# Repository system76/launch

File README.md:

# System76 Launch Configurable Keyboard

The System76 Launch Configurable Keyboard is designed to provide the ultimate
user controlled keyboard experience, with open source mechanical and electrical
design, open source firmware and associated software, and a large number of
user configuration opportunities. It is registered open source hardware with
[OSHWA UID US001062](https://certification.oshwa.org/us001062.html).

- [Mechanical Design](#mechanical-design)
- [Electrical Design](#electrical-design)
- [Firmware and Software](#firmware-and-software)

## Mechanical Design

### Open Source Chassis

The Launch chassis is licensed CC-BY-SA-4.0 and can be viewed in the
[chassis](./chassis/) folder using [FreeCAD](https://www.freecad.org).

### Milled Aluminum

The chassis is milled from two solid blocks of aluminum and powder coated to
provide excellent fit and finish. Each pocket, port, and hole is designed and
precisely machined so that swapping switches and plugging in cables is easy and
secure for the user.

### Detachable Lift Bar

The included lift bar can be magnetically secured to add 15 degrees of angle to
your keyboard for ergonomics.

### Innovative Layout

The layout is designed to provide a large number of remapping opportunities.
The default layout can be viewed
[here](http://www.keyboard-layout-editor.com/#/gists/8ec5e9026d616ebad6b2c7e9d943e7c0),
and the extra keys included can be viewed
[here](http://www.keyboard-layout-editor.com/#/gists/a3ad8710b27f78fd938077b2bf6d3ef5).

### Swappable Keycaps

The keycaps are PBT material with a dye sublimation legend and XDA profile to
provide excellent feel and lifespan. Extras are provided for common replacements
and color preference. An included keycap puller can be used to move and replace
the keycaps.

### Swappable Switches

The switches are mounted in sockets that support any RGB switch with an MX
compatible footprint. Examples are the Cherry MX RGB switches and the Kailh
BOX switches. Switches can be removed easily at any time with the included
switch puller.

## Electrical Design

### Open Source PCB

The Launch PCB is licensed GPLv3 and can be viewed in the
[pcb](./pcb/) folder using [KiCad](https://kicad.org/).

### Integrated Dock

Launch connects to a computer using the included USB-C to USB-C cable or USB-C
to USB-A cable. It supports USB 3.2 Gen 2 with speeds up to 10 Gbps with either
cable, provided the computer supports these speeds. It provides 2 USB-C and 2
USB-A connectors that also support USB 3.2 Gen 2, with the 10 Gbps bandwidth
shared between them on demand.

### Independent RGB Lighting

Each switch has an RGB LED that is independently controlled by firmware. This
allows for a number of RGB LED patterns to be selected.

### N-Key Rollover

The keyboard matrix uses diodes on all intersections, providing full independent
scanning of each key position.

## Firmware and Software

### Open Source Firmware

The Launch firmware is based on [QMK](https://github.com/system76/qmk_firmware),
licensed GPLv2, and the latest version is linked in the `firmware` submodule.

### Open Source Software

Projects that integrate with Launch are open source software, such as the
[System76 Keyboard Configurator](https://github.com/pop-os/keyboard-configurator),
licensed GPLv3, and [fwupd](https://github.com/fwupd/fwupd/), licensed LGPLv2.1.

### Easy Remapping

The keyboard can be remapped at runtime using the
[System76 Keyboard Configurator](https://github.com/pop-os/keyboard-configurator).
This utility runs on Linux, Mac OS, and Windows.

### Firmware Updates

Firmware updates are supported through the
[fwupd](https://github.com/fwupd/fwupd/) project, and are distributed using the
related Linux Vendor Firmware Service. Settings are stored on EEPROM and are
maintained through firmware updates.

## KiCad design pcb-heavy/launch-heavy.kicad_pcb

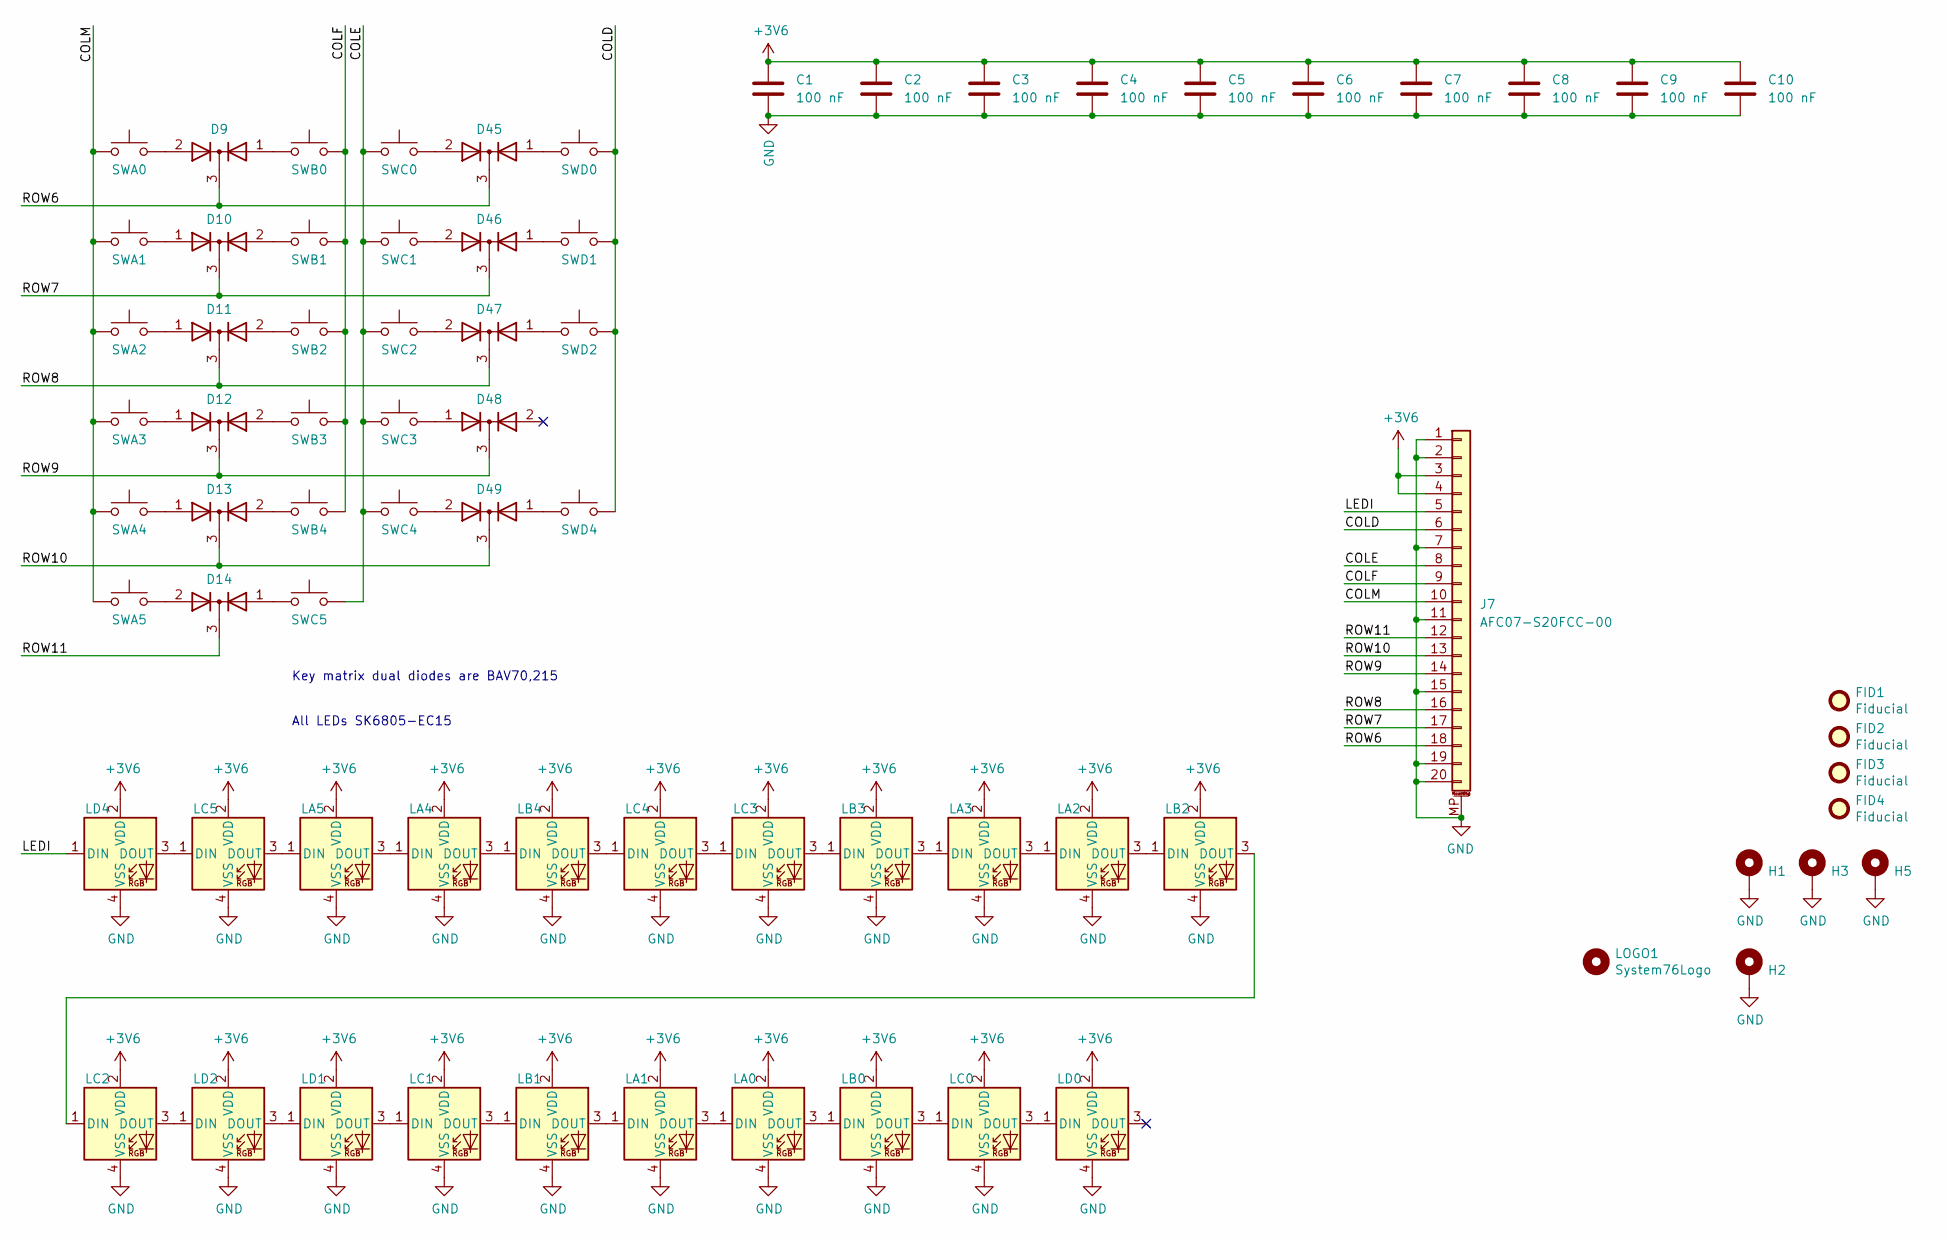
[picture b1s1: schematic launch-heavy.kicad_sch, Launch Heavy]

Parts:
C1, C2, C3, C4, C5, C6, C7, C8, C9, C10: 100 nF; C_0603_1608Metric
D9, D10, D11, D12, D13, D14, D45, D46, D47, D48, D49: BAV70,215; SOT-23
FID1, FID2, FID3, FID4: Fiducial; Fiducial_0.75mm_Mask1.5mm
H1, H2, H3, H5: MountingHole_Pad; MountingHole
J7: AFC07-S20FCC-00
LA0, LA1, LA2, LA3, LA4, LA5: SK6805-EC15; LED_SK6805-EC15
LB0, LB1, LB2, LB3, LB4: SK6805-EC15; LED_SK6805-EC15
LC0, LC1, LC2, LC3, LC4, LC5: SK6805-EC15; LED_SK6805-EC15
LD0, LD1, LD2, LD4: SK6805-EC15; LED_SK6805-EC15
LOGO1: System76Logo; System76
SWA0, SWA1, SWA2, SWA3, SWA4, SWA5: CPG151101S11; Kailh_socket_MX
SWB0, SWB1, SWB2, SWB3, SWB4: CPG151101S11; Kailh_socket_MX
SWC0, SWC1, SWC2, SWC3, SWC4, SWC5: CPG151101S11; Kailh_socket_MX
SWD0, SWD1, SWD2, SWD4: CPG151101S11; Kailh_socket_MX

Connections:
+3V6: C1.2, C2.2, C3.2, C4.2, C5.2, C6.2, C7.2, C8.2, C9.2, C10.2, J7.3, J7.4, LA0.2 (VDD), LA1.2 (VDD), LA2.2 (VDD), LA3.2 (VDD), LA4.2 (VDD), LA5.2 (VDD), LB0.2 (VDD), LB1.2 (VDD), LB2.2 (VDD), LB3.2 (VDD), LB4.2 (VDD), LC0.2 (VDD), LC1.2 (VDD), LC2.2 (VDD), LC3.2 (VDD), LC4.2 (VDD), LC5.2 (VDD), LD0.2 (VDD), LD1.2 (VDD), LD2.2 (VDD), LD4.2 (VDD)
/COLD: J7.6, SWD0.1, SWD1.1, SWD2.1, SWD4.1
/COLE: J7.8, SWC0.1, SWC1.1, SWC2.1, SWC3.1, SWC4.1, SWC5.1
/COLF: J7.9, SWB0.1, SWB1.1, SWB2.1, SWB3.1, SWB4.1
/COLM: J7.10, SWA0.1, SWA1.1, SWA2.1, SWA3.1, SWA4.1, SWA5.1
/LEDI: J7.5, LD4.1 (DIN)
/ROW6: D9.3 (K), D45.3 (K), J7.18
/ROW7: D10.3 (K), D46.3 (K), J7.17
/ROW8: D11.3 (K), D47.3 (K), J7.16
/ROW9: D12.3 (K), D48.3 (K), J7.14
/ROW10: D13.3 (K), D49.3 (K), J7.13
/ROW11: D14.3 (K), J7.12
GND: C1.1, C2.1, C3.1, C4.1, C5.1, C6.1, C7.1, C8.1, C9.1, C10.1, H1.1, H2.1, H3.1, H5.1, J7.1, J7.2, J7.7, J7.11, J7.15, J7.19, J7.20, J7.MP (MountPin), LA0.4 (VSS), LA1.4 (VSS), LA2.4 (VSS), LA3.4 (VSS), LA4.4 (VSS), LA5.4 (VSS), LB0.4 (VSS), LB1.4 (VSS), LB2.4 (VSS), LB3.4 (VSS), LB4.4 (VSS), LC0.4 (VSS), LC1.4 (VSS), LC2.4 (VSS), LC3.4 (VSS), LC4.4 (VSS), LC5.4 (VSS), LD0.4 (VSS), LD1.4 (VSS), LD2.4 (VSS), LD4.4 (VSS)
unnamed: D9.1 (A), SWB0.2
unnamed: D9.2 (A), SWA0.2
unnamed: D10.1 (A), SWA1.2
unnamed: D10.2 (A), SWB1.2
unnamed: D11.1 (A), SWA2.2
unnamed: D11.2 (A), SWB2.2
unnamed: D12.1 (A), SWA3.2
unnamed: D12.2 (A), SWB3.2
unnamed: D13.1 (A), SWA4.2
unnamed: D13.2 (A), SWB4.2
unnamed: D14.1 (A), SWC5.2
unnamed: D14.2 (A), SWA5.2
unnamed: D45.1 (A), SWD0.2
unnamed: D45.2 (A), SWC0.2
unnamed: D46.1 (A), SWD1.2
unnamed: D46.2 (A), SWC1.2
unnamed: D47.1 (A), SWD2.2
unnamed: D47.2 (A), SWC2.2
unnamed: D48.1 (A), SWC3.2
unnamed: D49.1 (A), SWD4.2
unnamed: D49.2 (A), SWC4.2
unnamed: LA0.1 (DIN), LA1.3 (DOUT)
unnamed: LA0.3 (DOUT), LB0.1 (DIN)
unnamed: LA1.1 (DIN), LB1.3 (DOUT)
unnamed: LA2.1 (DIN), LA3.3 (DOUT)
unnamed: LA2.3 (DOUT), LB2.1 (DIN)
unnamed: LA3.1 (DIN), LB3.3 (DOUT)
unnamed: LA4.1 (DIN), LA5.3 (DOUT)
unnamed: LA4.3 (DOUT), LB4.1 (DIN)
unnamed: LA5.1 (DIN), LC5.3 (DOUT)
unnamed: LB0.3 (DOUT), LC0.1 (DIN)
unnamed: LB1.1 (DIN), LC1.3 (DOUT)
unnamed: LB2.3 (DOUT), LC2.1 (DIN)
unnamed: LB3.1 (DIN), LC3.3 (DOUT)
unnamed: LB4.3 (DOUT), LC4.1 (DIN)
unnamed: LC0.3 (DOUT), LD0.1 (DIN)
unnamed: LC1.1 (DIN), LD1.3 (DOUT)
unnamed: LC2.3 (DOUT), LD2.1 (DIN)
unnamed: LC3.1 (DIN), LC4.3 (DOUT)
unnamed: LC5.1 (DIN), LD4.3 (DOUT)
unnamed: LD1.1 (DIN), LD2.3 (DOUT)

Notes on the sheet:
Key matrix dual diodes are BAV70,215
All LEDs SK6805-EC15

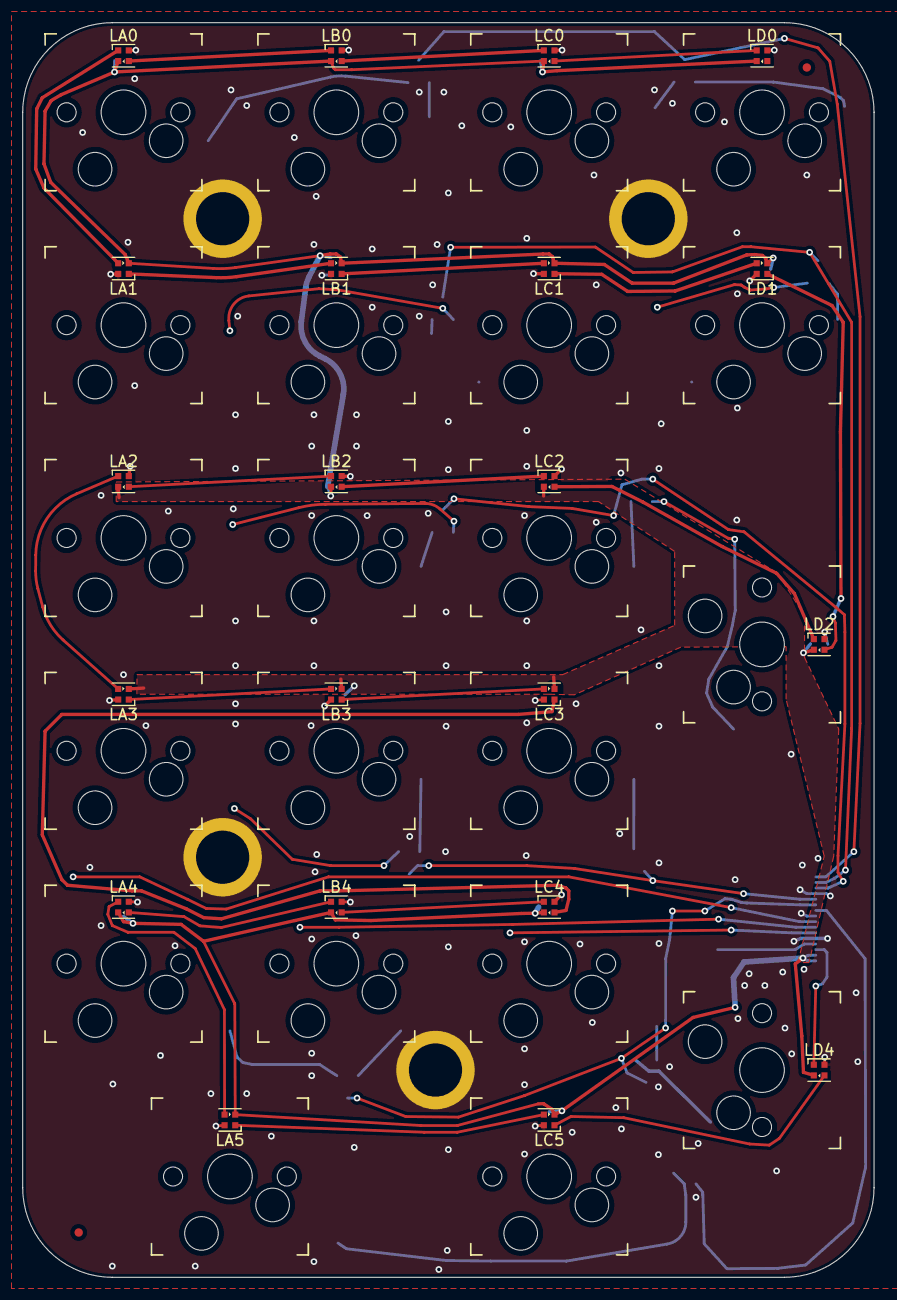
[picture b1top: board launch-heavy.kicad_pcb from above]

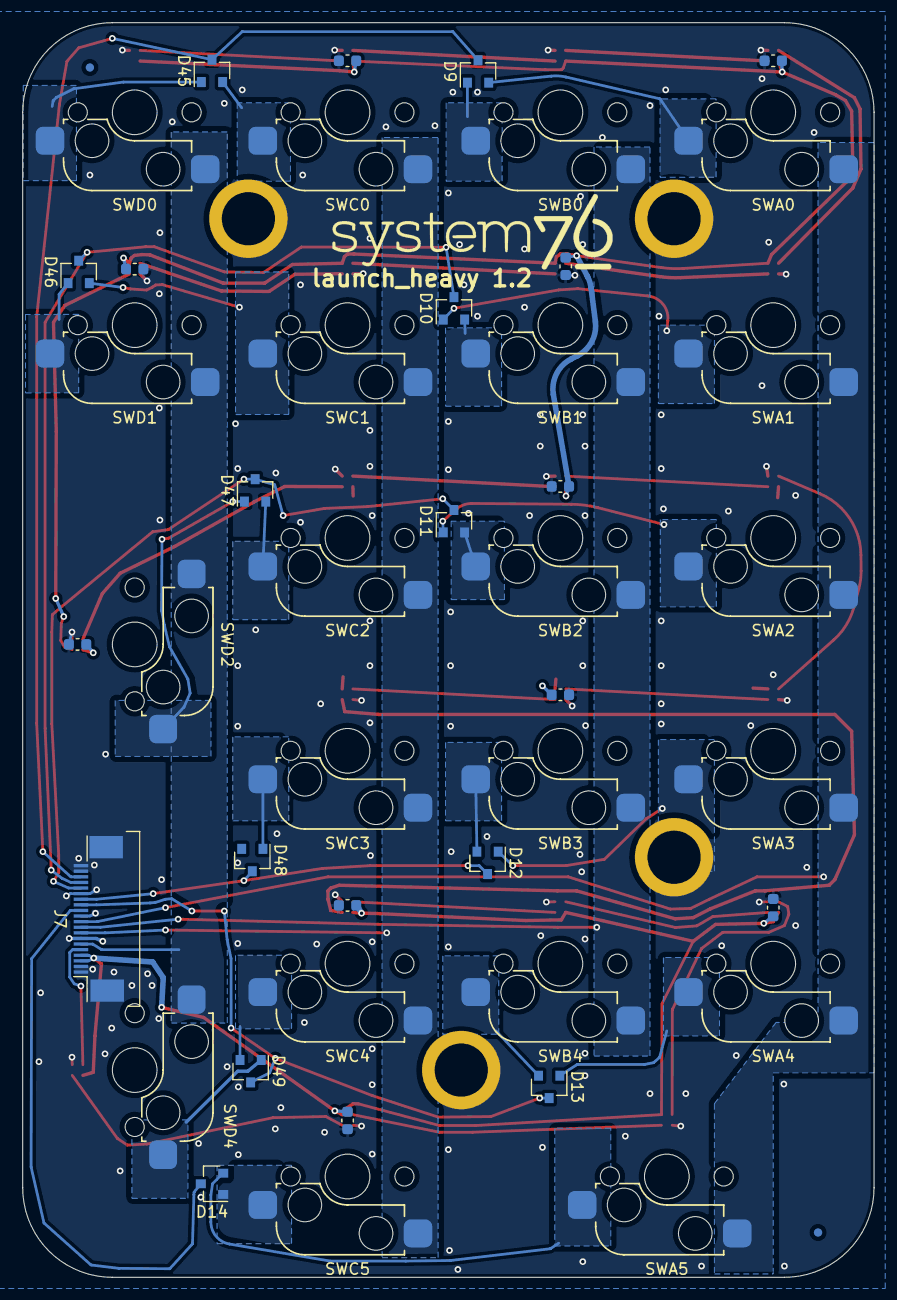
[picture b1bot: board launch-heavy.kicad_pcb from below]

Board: 2 copper layers, 76.0 x 112.0 mm, 73 parts (46 on the bottom side), 54 nets.

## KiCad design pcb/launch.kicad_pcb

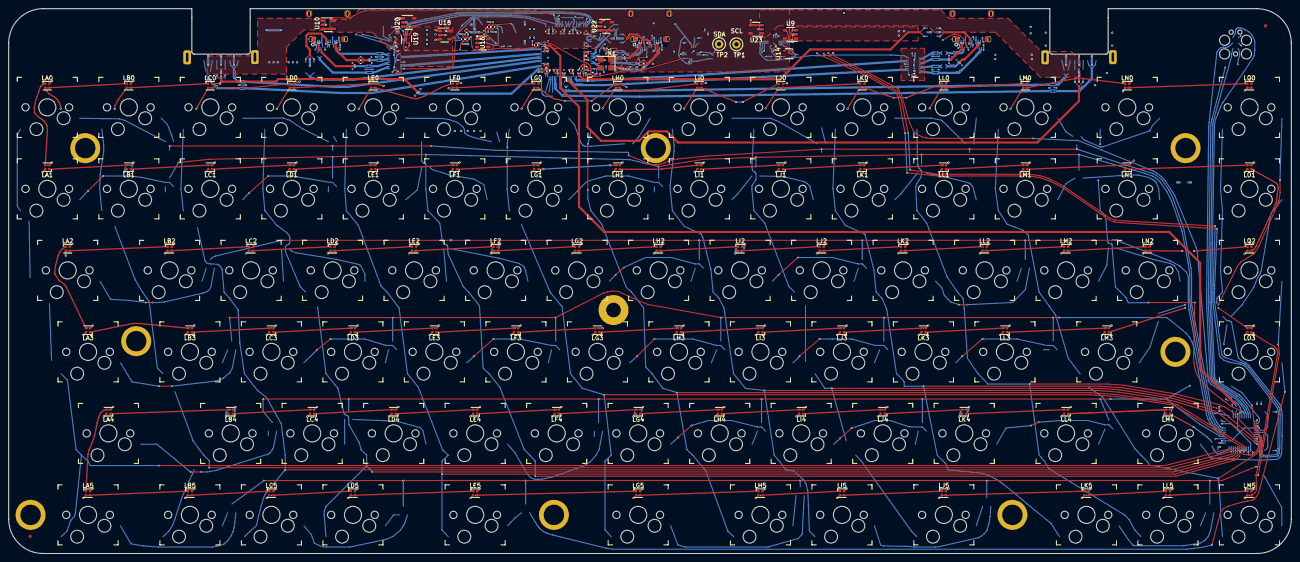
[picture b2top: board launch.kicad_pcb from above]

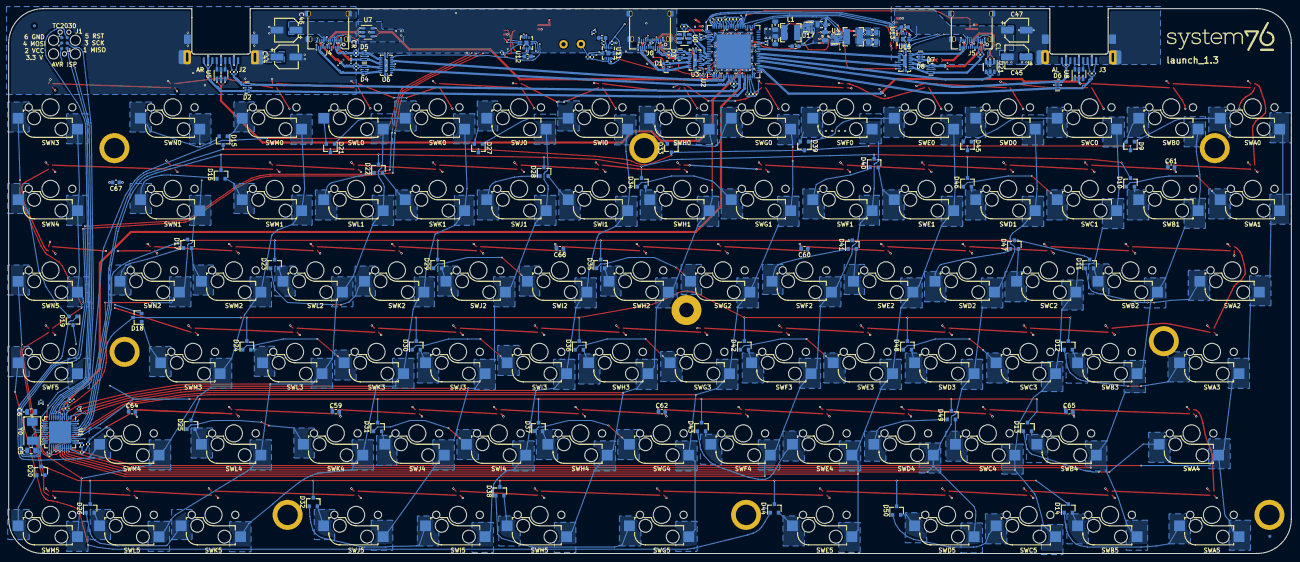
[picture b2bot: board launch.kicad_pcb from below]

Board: 4 copper layers, 299.0 x 127.0 mm, 372 parts (229 on the bottom side), 337 nets.

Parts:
C0, C1, C2, C3, C4, C8, C9, C10, C11, C12, C13, C14, C15, C16, C17, C18, C19, C20, C21, C22, C23, C24, C28, C29, C30, C31, C36, C37, C38, C39, C40, C41, C42, C43, C51, C52, C53, C54, C55, C56, C57, C58, C63: 0.1uF; C_0402_1005Metric
C5, C6: 22pF; C_0805_2012Metric
C7: 1 nF; C_0402_1005Metric
C25, C26, C27, C33, C59, C60, C61, C62, C64, C65, C66, C67: 2.2 uF; C_0603_1608Metric
C32, C34, C35, C48, C49, C50: 22 uF; C_0805_2012Metric
C44, C45, C46, C47: APXF6R3ARA151ME40G; CP_Elec_5x3.9
C68, C69: 330 pF; C_0402_1005Metric
D1, D2, D3, D4, D5, D6, D7, D8: PUSB3FR4Z; DFN-10_1x2.5mm_P0.5mm
D9, D10, D11, D12, D13, D14, D15, D16, D17, D18, D19, D20, D21, D22, D23, D24, D25, D26, D27, D28, D29, D30, D31, D32, D33, D34, D35, D36, D37, D38, D39, D40, D41, D42, D43, D44, D45, D46, D47, D48, D49, D50: BAV70,215; SOT-23
FID1, FID2, FID3, FID4: Fiducial; Fiducial_0.75mm_Mask1.5mm
H1, H2, H3, H4, H5, H6, H7, H8, H9: MountingHole_Pad; MountingHole
J0, J4, J5: 12401598E4#2A; USB_C_Receptacle_Amphenol_12401610E4-2A
J1: DNP; Tag-Connect_TC2030-IDC-FP_2x03_P1.27mm_Vertical
J2, J3: 1003-002-01100; USB3_A_CnC_Tech_1003-002-01100
L1, L2: SRN4018TA-2R2M; L_Bourns-SRN4018
LA0, LA1, LA2, LA3, LA4, LA5: SK6805-EC15; LED_SK6805-EC15
LB0, LB1, LB2, LB3, LB4, LB5: SK6805-EC15; LED_SK6805-EC15
LC0, LC1, LC2, LC3, LC4, LC5: SK6805-EC15; LED_SK6805-EC15
LD0, LD1, LD2, LD3, LD4, LD5: SK6805-EC15; LED_SK6805-EC15
LE0, LE1, LE2, LE3, LE4, LE5: SK6805-EC15; LED_SK6805-EC15
LF0, LF1, LF2, LF3, LF4: SK6805-EC15; LED_SK6805-EC15
LG0, LG1, LG2, LG3, LG4, LG5: SK6805-EC15; LED_SK6805-EC15
LH0, LH1, LH2, LH3, LH4, LH5: SK6805-EC15; LED_SK6805-EC15
LI0, LI1, LI2, LI3, LI4, LI5: SK6805-EC15; LED_SK6805-EC15
LJ0, LJ1, LJ2, LJ3, LJ4, LJ5: SK6805-EC15; LED_SK6805-EC15
LK0, LK1, LK2, LK3, LK4, LK5: SK6805-EC15; LED_SK6805-EC15
LL0, LL1, LL2, LL3, LL4, LL5: SK6805-EC15; LED_SK6805-EC15
LM0, LM1, LM2, LM3, LM4, LM5: SK6805-EC15; LED_SK6805-EC15
LN0, LN1, LN2: SK6805-EC15; LED_SK6805-EC15
LO0, LO1, LO2, LO3: SK6805-EC15; LED_SK6805-EC15
LOGO1: System76Logo; System76
R1: 12 k; R_0402_1005Metric
R2, R3: 22; R_0402_1005Metric
R4, R5, R6, R7, R8, R11, R15, R23, R26, R31, R32: 10 k; R_0402_1005Metric
R9, R10, R14: 9.1 k; R_0402_1005Metric
R12, R13, R19, R20: 200 k; R_0402_1005Metric
R16, R17, R29, R30: 100 k; R_0402_1005Metric
R18, R21: 43 k; R_0402_1005Metric
R22, R25, R28: 52.3 k; R_0402_1005Metric
R24, R33, R34: DNP; R_0402_1005Metric
R27: 499; R_0402_1005Metric
SWA0, SWA1, SWA2, SWA3, SWA4, SWA5: CPG151101S11; Kailh_socket_MX
SWB0, SWB1, SWB2, SWB3, SWB4, SWB5: CPG151101S11; Kailh_socket_MX
SWC0, SWC1, SWC2, SWC3, SWC4, SWC5: CPG151101S11; Kailh_socket_MX
SWD0, SWD1, SWD2, SWD3, SWD4, SWD5: CPG151101S11; Kailh_socket_MX
SWE0, SWE1, SWE2, SWE3, SWE4, SWE5: CPG151101S11; Kailh_socket_MX
SWF0, SWF1, SWF2, SWF3, SWF4, SWF5: CPG151101S11; Kailh_socket_MX
SWG0, SWG1, SWG2, SWG3, SWG4, SWG5: CPG151101S11; Kailh_socket_MX
SWH0, SWH1, SWH2, SWH3, SWH4, SWH5: CPG151101S11; Kailh_socket_MX
SWI0, SWI1, SWI2, SWI3, SWI4, SWI5: CPG151101S11; Kailh_socket_MX
SWJ0, SWJ1, SWJ2, SWJ3, SWJ4, SWJ5: CPG151101S11; Kailh_socket_MX
SWK0, SWK1, SWK2, SWK3, SWK4, SWK5: CPG151101S11; Kailh_socket_MX
SWL0, SWL1, SWL2, SWL3, SWL4, SWL5: CPG151101S11; Kailh_socket_MX
SWM0, SWM1, SWM2, SWM3, SWM4, SWM5: CPG151101S11; Kailh_socket_MX
SWN0, SWN1, SWN2, SWN3, SWN4, SWN5: CPG151101S11; Kailh_socket_MX
TP1, TP2: DNP; TestPoint_Loop_D1.80mm_Drill1.0mm_Beaded
U0, U5, U7, U8, U21: USBLC6-2SC6; SOT-23-6
U1: ATmega32U4-MU; QFN-44-1EP_7x7mm_P0.5mm_EP5.2x5.2mm
U2: USB7216C; QFN-100-1EP_12x12mm_P0.4mm_EP8x8mm
U3, U6, U15: CBTL02043ABQ,115; QFN-20-1EP_2.5x4.5mm_P0.5mm_EP1x3mm
U4, U17: AP3441LSHE-7B; W-DFN2020-8_Type_C
U9, U10, U20, U22, U23: AP22811AW5-7; SOT-23-5
U11: PTN5110DHQ; QFN-16-1EP_2.6x2.6mm_P0.4mm_EP1.1x1mm
U12, U13: PTN5110THQ; QFN-16-1EP_2.6x2.6mm_P0.4mm_EP1.1x1mm
U14, U19: SN74LVC1G08DCKR; SOT-353_SC-70-5
U16: AP22811AW5-7‎; SOT-23-5
U18: LP5907MFX-3.3; SOT-23-5
X1: ECS-3225MV-250-BN-TR; Oscillator_SMD_SeikoEpson_SG8002CE-4Pin_3.2x2.5mm
Y0: ECS-160-18-23G-JGN-TR; Crystal_SMD_0603-2Pin_6.0x3.5mm

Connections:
+1V1: C8.1, C17.1, C18.1, C19.1, C20.1, C21.1, C22.1, C23.1, C24.1, C34.1, C50.1, C68.1, L1.2, R14.1, U2.9, U2.18, U2.25, U2.31, U2.38, U2.55, U2.78, U2.85, U2.93
+3V3: C0.2, C1.1, C2.1, C3.1, C33.1, C36.1, C37.1, C38.1, C39.1, C40.1, C41.1, C42.1, C43.1, C55.1, C56.1, C57.1, C58.1, C63.1, J1.2, R5.1, R6.1, R7.1, R9.1, R10.1, R23.1, R31.1, R32.1, U1.6, U1.14, U1.24, U1.34, U1.44, U2.26, U2.43, U2.53, U2.62, U2.67, U2.79, U2.81, U2.82, U2.88, U2.99, U3.1, U3.6, U3.10, U6.1, U6.6, U6.10, U11.3, U11.11, U12.3, U12.11, U13.3, U13.11, U15.1, U15.6, U15.10, U18.5, X1.1, X1.4
+3V6: C35.1, C49.1, C59.1, C60.1, C61.1, C62.1, C64.1, C65.1, C66.1, C67.1, C69.1, L2.2, LA0.2, LA1.2, LA2.2, LA3.2, LA4.2, LA5.2, LB0.2, LB1.2, LB2.2, LB3.2, LB4.2, LB5.2, LC0.2, LC1.2, LC2.2, LC3.2, LC4.2, LC5.2, LD0.2, LD1.2, LD2.2, LD3.2, LD4.2, LD5.2, LE0.2, LE1.2, LE2.2, LE3.2, LE4.2, LE5.2, LF0.2, LF1.2, LF2.2, LF3.2, LF4.2, LG0.2, LG1.2, LG2.2, LG3.2, LG4.2, LG5.2, LH0.2, LH1.2, LH2.2, LH3.2, LH4.2, LH5.2, LI0.2, LI1.2, LI2.2, LI3.2, LI4.2, LI5.2, LJ0.2, LJ1.2, LJ2.2, LJ3.2, LJ4.2, LJ5.2, LK0.2, LK1.2, LK2.2, LK3.2, LK4.2, LK5.2, LL0.2, LL1.2, LL2.2, LL3.2, LL4.2, LL5.2, LM0.2, LM1.2, LM2.2, LM3.2, LM4.2, LM5.2, LN0.2, LN1.2, LN2.2, LO0.2, LO1.2, LO2.2, LO3.2, R25.1, U18.1, U18.3
/AVR_SCL: R9.2, TP1.1, U1.18, U2.75, U11.8, U12.8, U13.8
/AVR_SDA: R10.2, TP2.1, U1.19, U2.76, U11.7, U12.7, U13.7
/USB/AL_D+: U2.28, U8.1
/USB/AL_D-: U2.27, U8.3
/USB/AL_ESD_D+: J3.3, U8.6
/USB/AL_ESD_D-: J3.2, U8.4
/USB/AL_RX+: D6.2, D6.9, J3.6, U2.32
/USB/AL_RX-: D6.1, D6.10, J3.5, U2.33
/USB/AL_TX+: C54.1, D6.5, D6.6, U2.29
/USB/AL_TX-: C53.1, D6.4, D6.7, U2.30
/USB/AL_VBUS: C45.1, J3.1, U8.5, U10.1
/USB/AR_D+: U2.15, U5.1
/USB/AR_D-: U2.14, U5.3
/USB/AR_ESD_D+: J2.3, U5.6
/USB/AR_ESD_D-: J2.2, U5.4
/USB/AR_RX+: D2.2, D2.9, J2.6, U2.19
/USB/AR_RX-: D2.1, D2.10, J2.5, U2.20
/USB/AR_TX+: C52.1, D2.5, D2.6, U2.16
/USB/AR_TX-: C51.1, D2.4, D2.7, U2.17
/USB/AR_VBUS: C44.1, J2.1, U5.5, U23.1
/USB/AVR_USB_D+: R2.2, U2.42
/USB/AVR_USB_D-: R3.1, U2.41
/USB/AVR_VBUS: C4.1, R24.2, U1.7, U22.1
/USB/CL_BYP: C27.2, U13.4, U19.5
/USB/CL_CC1: J5.A5, U13.13
/USB/CL_CC2: J5.B5, U13.14
/USB/CL_D0+: J5.A6, J5.B6, U21.1
/USB/CL_D0-: J5.A7, J5.B7, U21.3
/USB/CL_D+: U2.34, U21.6
/USB/CL_D-: U2.35, U21.4
/USB/CL_EN: U19.4, U20.4
/USB/CL_RX1+: D7.2, D7.9, J5.B11, U15.14
/USB/CL_RX1-: D7.1, D7.10, J5.B10, U15.15
/USB/CL_RX2+: D8.5, D8.6, J5.A11, U15.19
/USB/CL_RX2-: D8.4, D8.7, J5.A10, U15.18
/USB/CL_RX+: U2.39, U15.4
/USB/CL_RX-: U2.40, U15.3
/USB/CL_SEL: U2.51, U15.9
/USB/CL_SRC: R16.1, U13.16, U19.1
/USB/CL_TX1+: C30.1, D7.5, D7.6, U15.12
/USB/CL_TX1-: C28.1, D7.4, D7.7, U15.13
/USB/CL_TX1D+: C30.2, J5.A2
/USB/CL_TX1D-: C28.2, J5.A3
/USB/CL_TX2+: C31.1, D8.1, D8.10, U15.16
/USB/CL_TX2-: C29.1, D8.2, D8.9, U15.17
/USB/CL_TX2D+: C31.2, J5.B3
/USB/CL_TX2D-: C29.2, J5.B2
/USB/CL_TX+: U2.36, U15.8
/USB/CL_TX-: U2.37, U15.7
/USB/CL_VBUS: C47.1, J5.A4, J5.A9, J5.B4, J5.B9, U13.15, U20.1, U21.5
/USB/CR_BYP: C26.2, U12.4, U14.5
/USB/CR_CC1: J4.A5, U12.13
/USB/CR_CC2: J4.B5, U12.14
/USB/CR_D0+: J4.A6, J4.B6, U7.1
/USB/CR_D0-: J4.A7, J4.B7, U7.3
/USB/CR_D+: U2.5, U7.6
/USB/CR_D-: U2.6, U7.4
/USB/CR_EN: U9.4, U14.4
/USB/CR_RX1+: D4.1, D4.10, J4.A11, U6.19
/USB/CR_RX1-: D4.2, D4.9, J4.A10, U6.18
/USB/CR_RX2+: D5.5, D5.6, J4.B10, U6.15
/USB/CR_RX2-: D5.4, D5.7, J4.B11, U6.14
/USB/CR_RX+: U2.11, U6.3
/USB/CR_RX-: U2.10, U6.4
/USB/CR_SEL: U2.73, U6.9
/USB/CR_SRC: R17.1, U12.16, U14.1
/USB/CR_TX1+: C13.1, D4.4, D4.7, U6.17
/USB/CR_TX1-: C15.1, D4.5, D4.6, U6.16
/USB/CR_TX1D+: C15.2, J4.B3
/USB/CR_TX1D-: C13.2, J4.B2
/USB/CR_TX2+: C14.1, D5.2, D5.9, U6.13
/USB/CR_TX2-: C16.1, D5.1, D5.10, U6.12
/USB/CR_TX2D+: C16.2, J4.A2
/USB/CR_TX2D-: C14.2, J4.A3
/USB/CR_TX+: U2.8, U6.7
/USB/CR_TX-: U2.7, U6.8
/USB/CR_VBUS: C46.1, J4.A4, J4.A9, J4.B4, J4.B9, U7.5, U9.1, U12.15
/USB/CS1: R11.1, U2.21
/USB/CS2: R12.1, U2.22
/USB/CS3: R13.1, U2.23
/USB/DP1_CC1: R33.1, U2.12
/USB/DP1_CC2: R34.1, U2.13
/USB/HUB_SCL: R31.2, U2.61
/USB/HUB_SDA: R32.2, U2.3
/USB/PRT_CTL1: U2.60, U9.3, U14.2
/USB/PRT_CTL2: U2.59, U23.3, U23.4
/USB/PRT_CTL3: U2.58, U10.3, U10.4
/USB/PRT_CTL4: U2.57, U19.2, U20.3
/USB/PRT_CTL6: U2.77, U22.3, U22.4
/USB/RBIAS: R1.1, U2.100
/USB/SPI_CLK: R29.1, U2.68
/USB/SPI_D0: R19.1, U2.70
/USB/SPI_D1: R30.1, U2.71
/USB/SPI_~CE: R20.1, U2.69
/USB/TEST1: R5.2, U2.63
/USB/TEST2: R6.2, U2.64
/USB/TEST3: R7.2, U2.65
/USB/UP_ADDR: R8.1, U11.5
/USB/UP_BYP: C25.2, R8.2, U11.4
/USB/UP_CC1: J0.A5, U11.13
/USB/UP_CC2: J0.B5, U11.14
/USB/UP_D0+: J0.A6, J0.B6, U0.1
/USB/UP_D0-: J0.A7, J0.B7, U0.3
/USB/UP_D1+: U0.6, U2.89
/USB/UP_D1-: U0.4, U2.90
/USB/UP_RX1+: D3.2, D3.9, J0.B11, U3.14
/USB/UP_RX1-: D3.1, D3.10, J0.B10, U3.15
/USB/UP_RX2+: D1.5, D1.6, J0.A11, U3.19
/USB/UP_RX2-: D1.4, D1.7, J0.A10, U3.18
/USB/UP_SEL: U2.74, U3.9
/USB/UP_TX1+: C12.1, D3.4, D3.7, U3.13
/USB/UP_TX1-: C11.1, D3.5, D3.6, U3.12
/USB/UP_TX1D+: C12.2, J0.A3
/USB/UP_TX1D-: C11.2, J0.A2
/USB/UP_TX2+: C9.1, D1.2, D1.9, U3.17
/USB/UP_TX2-: C10.1, D1.1, D1.10, U3.16
/USB/UP_TX2D+: C9.2, J0.B2
/USB/UP_TX2D-: C10.2, J0.B3
/USB/USB_UP_RX+: U2.94, U3.4
/USB/USB_UP_RX-: U2.95, U3.3
/USB/USB_UP_TX+: U2.91, U3.8
/USB/USB_UP_TX-: U2.92, U3.7
/USB/VBUS_DET: R21.2, R22.1, U2.2
/USB/VBUS_MON: R18.2, R28.1, U2.80
/USB/XTALI: U2.98, X1.3
/USB/~RESET: C7.1, R23.2, U2.1, U4.2, U17.2
/power/FB1V1: C68.2, R14.2, R15.1, U17.1
/power/FB3V6: C69.2, R25.2, R26.1, U4.1
/power/SW1V1: L1.1, U17.6
/power/SW3V6: L2.1, U4.6
COLA: SWA0.1, SWA1.1, SWA2.1, SWA3.1, SWA4.1, SWA5.1, U1.27
COLB: SWB0.1, SWB1.1, SWB2.1, SWB3.1, SWB4.1, SWB5.1, U1.32
COLC: SWC0.1, SWC1.1, SWC2.1, SWC3.1, SWC4.1, SWC5.1, U1.31
COLD: SWD0.1, SWD1.1, SWD2.1, SWD3.1, SWD4.1, SWD5.1, U1.30
COLE: SWE0.1, SWE1.1, SWE2.1, SWE3.1, SWE4.1, SWE5.1, U1.29
COLF: SWF0.1, SWF1.1, SWF2.1, SWF3.1, SWF4.1, SWF5.1, U1.28
COLG: SWG0.1, SWG1.1, SWG2.1, SWG3.1, SWG4.1, SWG5.1, U1.26
COLH: SWH0.1, SWH1.1, SWH2.1, SWH3.1, SWH4.1, SWH5.1, U1.25
COLI: SWI0.1, SWI1.1, SWI2.1, SWI3.1, SWI4.1, SWI5.1, U1.1
COLJ: SWJ0.1, SWJ1.1, SWJ2.1, SWJ3.1, SWJ4.1, SWJ5.1, U1.22
COLK: SWK0.1, SWK1.1, SWK2.1, SWK3.1, SWK4.1, SWK5.1, U1.21
COLL: SWL0.1, SWL1.1, SWL2.1, SWL3.1, SWL4.1, SWL5.1, U1.20
COLM: SWM0.1, SWM1.1, SWM2.1, SWM3.1, SWM4.1, SWM5.1, U1.12
COLN: SWN0.1, SWN1.1, SWN2.1, SWN3.1, SWN4.1, SWN5.1, U1.8
GND: C0.1, C1.2, C2.2, C3.2, C4.2, C5.2, C6.2, C7.2, C8.2, C17.2, C18.2, C19.2, C20.2, C21.2, C22.2, C23.2, C24.2, C25.1, C26.1, C27.1, C32.2, C33.2, C34.2, C35.2, C36.2, C37.2, C38.2, C39.2, C40.2, C41.2, C42.2, C43.2, C44.2, C45.2, C46.2, C47.2, C48.2, C49.2, C50.2, C55.2, C56.2, C57.2, C58.2, C59.2, C60.2, C61.2, C62.2, C63.2, C64.2, C65.2, C66.2, C67.2, D1.3, D1.8, D2.3, D2.8, D3.3, D3.8, D4.3, D4.8, D5.3, D5.8, D6.3, D6.8, D7.3, D7.8, D8.3, D8.8, H1.1, H2.1, H3.1, H4.1, H5.1, H6.1, H7.1, H8.1, H9.1, J0.A1, J0.A12, J0.B1, J0.B12, J0.S1, J1.6, J2.4, J2.7, J2.10, J3.4, J3.7, J3.10, J4.A1, J4.A12, J4.B1, J4.B12, J4.S1, J5.A1, J5.A12, J5.B1, J5.B12, J5.S1, LA0.4, LA1.4, LA2.4, LA3.4, LA4.4, LA5.4, LB0.4, LB1.4, LB2.4, LB3.4, LB4.4, LB5.4, LC0.4, LC1.4, LC2.4, LC3.4, LC4.4, LC5.4, LD0.4, LD1.4, LD2.4, LD3.4, LD4.4, LD5.4, LE0.4, LE1.4, LE2.4, LE3.4, LE4.4, LE5.4, LF0.4, LF1.4, LF2.4, LF3.4, LF4.4, LG0.4, LG1.4, LG2.4, LG3.4, LG4.4, LG5.4, LH0.4, LH1.4, LH2.4, LH3.4, LH4.4, LH5.4, LI0.4, LI1.4, LI2.4, LI3.4, LI4.4, LI5.4, LJ0.4, LJ1.4, LJ2.4, LJ3.4, LJ4.4, LJ5.4, LK0.4, LK1.4, LK2.4, LK3.4, LK4.4, LK5.4, LL0.4, LL1.4, LL2.4, LL3.4, LL4.4, LL5.4, LM0.4, LM1.4, LM2.4, LM3.4, LM4.4, LM5.4, LN0.4, LN1.4, LN2.4, LO0.4, LO1.4, LO2.4, LO3.4, R1.2, R4.2, R11.2, R12.2, R13.2, R15.2, R16.2, R17.2, R19.2, R20.2, R22.2, R26.2, R28.2, R29.2, R30.2, R33.2, R34.2, U0.2, U1.5, U1.15, U1.23, U1.35, U1.43, U1.45, U2.24, U2.101, U3.2, U3.5, U3.11, U3.20, U3.21, U4.4, U4.8, U4.9, U5.2, U6.2, U6.5, U6.11, U6.20, U6.21, U7.2, U8.2, U9.2, U10.2, U11.17, U12.5, U12.17, U13.17, U14.3, U15.2, U15.5, U15.11, U15.20, U15.21, U16.2, U17.4, U17.8, U17.9, U18.2, U19.3, U20.2, U21.2, U22.2, U23.2, X1.2
LED: R4.1, R27.2, U1.33
MISO: J1.1, U1.11
MOSI: J1.4, U1.10
unnamed: C5.1, U1.17, Y0.2
unnamed: C6.1, U1.16, Y0.1
unnamed: C51.2, J2.8
unnamed: C52.2, J2.9
unnamed: C53.2, J3.8
unnamed: C54.2, J3.9
unnamed: D9.1, SWA0.2
unnamed: D9.2, SWB0.2
unnamed: D10.1, SWA1.2
unnamed: D10.2, SWB1.2
unnamed: D11.1, SWA2.2
unnamed: D11.2, SWB2.2
unnamed: D12.1, SWA3.2
unnamed: D12.2, SWB3.2
unnamed: D13.1, SWA4.2
unnamed: D13.2, SWB4.2
unnamed: D14.1, SWA5.2
unnamed: D14.2, SWB5.2
unnamed: D15.1, SWM0.2
unnamed: D15.2, SWN0.2
unnamed: D16.1, SWN1.2
unnamed: D16.2, SWM1.2
unnamed: D17.1, SWN2.2
unnamed: D17.2, SWM2.2
unnamed: D18.1, SWM3.2
unnamed: D18.2, SWN3.2
unnamed: D19.1, SWM4.2
unnamed: D19.2, SWN4.2
unnamed: D20.1, SWM5.2
unnamed: D20.2, SWN5.2
unnamed: D21.1, SWK0.2
unnamed: D21.2, SWL0.2
unnamed: D22.1, SWL1.2
unnamed: D22.2, SWK1.2
unnamed: D23.1, SWK2.2
unnamed: D23.2, SWL2.2
unnamed: D24.1, SWK3.2
unnamed: D24.2, SWL3.2
unnamed: D25.1, SWK4.2
unnamed: D25.2, SWL4.2
unnamed: D26.1, SWK5.2
unnamed: D26.2, SWL5.2
unnamed: D27.1, SWI0.2
unnamed: D27.2, SWJ0.2
unnamed: D28.1, SWJ1.2
unnamed: D28.2, SWI1.2
unnamed: D29.1, SWI2.2
unnamed: D29.2, SWJ2.2
unnamed: D30.1, SWI3.2
unnamed: D30.2, SWJ3.2
unnamed: D31.1, SWI4.2
unnamed: D31.2, SWJ4.2
unnamed: D32.1, SWI5.2
unnamed: D32.2, SWJ5.2
unnamed: D33.1, SWG0.2
unnamed: D33.2, SWH0.2
unnamed: D34.1, SWG1.2
unnamed: D34.2, SWH1.2
unnamed: D35.1, SWG2.2
unnamed: D35.2, SWH2.2
unnamed: D36.1, SWG3.2
unnamed: D36.2, SWH3.2
unnamed: D37.1, SWG4.2
unnamed: D37.2, SWH4.2
unnamed: D38.1, SWG5.2
unnamed: D38.2, SWH5.2
unnamed: D39.1, SWE0.2
unnamed: D39.2, SWF0.2
unnamed: D40.1, SWF1.2
unnamed: D40.2, SWE1.2
unnamed: D41.1, SWF2.2
unnamed: D41.2, SWE2.2
unnamed: D42.1, SWE3.2
unnamed: D42.2, SWF3.2
unnamed: D43.1, SWE4.2
unnamed: D43.2, SWF4.2
unnamed: D44.1, SWF5.2
unnamed: D44.2, SWE5.2
unnamed: D45.1, SWC0.2
unnamed: D45.2, SWD0.2
unnamed: D46.1, SWC1.2
unnamed: D46.2, SWD1.2
unnamed: D47.1, SWD2.2
unnamed: D47.2, SWC2.2
unnamed: D48.1, SWC3.2
unnamed: D48.2, SWD3.2
unnamed: D49.1, SWD4.2
unnamed: D49.2, SWC4.2
unnamed: D50.1, SWC5.2
unnamed: D50.2, SWD5.2
unnamed: LA0.1, LA1.3
unnamed: LA0.3, LB0.1
unnamed: LA1.1, LB1.3
unnamed: LA2.1, LA3.3
unnamed: LA2.3, LB2.1
unnamed: LA3.1, LB3.3
unnamed: LA4.1, LB4.3
unnamed: LA4.3, LA5.1
unnamed: LA5.3, LB5.1
unnamed: LB0.3, LC0.1
unnamed: LB1.1, LC1.3
unnamed: LB2.3, LC2.1
unnamed: LB3.1, LC3.3
unnamed: LB4.1, LC4.3
unnamed: LB5.3, LC5.1
unnamed: LC0.3, LD0.1
unnamed: LC1.1, LD1.3
unnamed: LC2.3, LD2.1
unnamed: LC3.1, LD3.3
unnamed: LC4.1, LD4.3
unnamed: LC5.3, LD5.1
unnamed: LD0.3, LE0.1
unnamed: LD1.1, LE1.3
unnamed: LD2.3, LE2.1
unnamed: LD3.1, LE3.3
unnamed: LD4.1, LE4.3
unnamed: LD5.3, LE5.1
unnamed: LE0.3, LF0.1
unnamed: LE1.1, LF1.3
unnamed: LE2.3, LF2.1
unnamed: LE3.1, LF3.3
unnamed: LE4.1, LF4.3
unnamed: LE5.3, LG5.1
unnamed: LF0.3, LG0.1
unnamed: LF1.1, LG1.3
unnamed: LF2.3, LG2.1
unnamed: LF3.1, LG3.3
unnamed: LF4.1, LG4.3
unnamed: LG0.3, LH0.1
unnamed: LG1.1, LH1.3
unnamed: LG2.3, LH2.1
unnamed: LG3.1, LH3.3
unnamed: LG4.1, LH4.3
unnamed: LG5.3, LH5.1
unnamed: LH0.3, LI0.1
unnamed: LH1.1, LI1.3
unnamed: LH2.3, LI2.1
unnamed: LH3.1, LI3.3
unnamed: LH4.1, LI4.3
unnamed: LH5.3, LI5.1
unnamed: LI0.3, LJ0.1
unnamed: LI1.1, LJ1.3
unnamed: LI2.3, LJ2.1
unnamed: LI3.1, LJ3.3
unnamed: LI4.1, LJ4.3
unnamed: LI5.3, LJ5.1
unnamed: LJ0.3, LK0.1
unnamed: LJ1.1, LK1.3
unnamed: LJ2.3, LK2.1
unnamed: LJ3.1, LK3.3
unnamed: LJ4.1, LK4.3
unnamed: LJ5.3, LK5.1
unnamed: LK0.3, LL0.1
unnamed: LK1.1, LL1.3
unnamed: LK2.3, LL2.1
unnamed: LK3.1, LL3.3
unnamed: LK4.1, LL4.3
unnamed: LK5.3, LL5.1
unnamed: LL0.3, LM0.1
unnamed: LL1.1, LM1.3
unnamed: LL2.3, LM2.1
unnamed: LL3.1, LM3.3
unnamed: LL4.1, LM4.3
unnamed: LL5.3, LM5.1
unnamed: LM0.3, LN0.1
unnamed: LM1.1, LN1.3
unnamed: LM2.3, LN2.1
unnamed: LM3.1, LO3.3
unnamed: LM4.1, R27.1
unnamed: LM5.3, LO3.1
unnamed: LN0.3, LO0.1
unnamed: LN1.1, LO1.3
unnamed: LN2.3, LO2.1
unnamed: LO1.1, LO2.3
unnamed: R2.1, U1.4
unnamed: R3.2, U1.3
ROW0: D9.3, D15.3, D21.3, D27.3, D33.3, D39.3, D45.3, U1.41
ROW1: D10.3, D16.3, D22.3, D28.3, D34.3, D40.3, D46.3, U1.40
ROW2: D11.3, D17.3, D23.3, D29.3, D35.3, D41.3, D47.3, U1.39
ROW3: D12.3, D18.3, D24.3, D30.3, D36.3, D42.3, D48.3, U1.38
ROW4: D13.3, D19.3, D25.3, D31.3, D37.3, D43.3, D49.3, U1.37
ROW5: D14.3, D20.3, D26.3, D32.3, D38.3, D44.3, D50.3, U1.36
RST: J1.5, U1.13
SCLK: J1.3, U1.9
VBUS: J0.A4, J0.A9, J0.B4, J0.B9, R18.1, R21.1, R24.1, U0.5, U9.5, U10.5, U11.12, U11.15, U12.12, U13.12, U16.4, U16.5, U20.5, U22.5, U23.5
VCC: C32.1, C48.1, U4.3, U4.7, U16.1, U17.3, U17.7

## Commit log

2019-12-05 init
2019-12-05 Add switch footprint
2019-12-08 Add placeholders
2020-03-05 Rename to launch, add matrix and EC support structure
2020-03-05 Set all references
2020-03-06 Add keyswitch footprints
2020-03-06 Fix references to switches and diodes
2020-03-06 Position switches in PCB
2020-03-06 Route first row
2020-03-07 Finish routing of matrix
2020-03-07 Cleanup tracks
2020-03-07 Add RBG LED matrix
2020-03-07 Route LEDs
2020-03-07 Route rows to EC
2020-03-08 Connect everything in schematic
2020-03-09 Route LED data in to EC
2020-03-09 Reduce board size
2020-03-09 Reroute to remove space at top of board
2020-03-10 Add ICSP header and add socket model
2020-03-10 Add BOM
2020-03-10 Add ISP header to BOM
2020-05-08 Add Kailh switch model to socket footprint
2020-07-23 work in progress on USB hub addition Incomplete: USB Vbus caps on all 4 downstream ports reset to hub review checklist and eval board design C left ESD, etc key matrix ESD 1.1 V may need to be 1.15 V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
2020-07-23 add data sheets
2020-07-29 USB hub schematic Review USB7206 checklist, implement changes added pull down resistors to source enable on TCPCs added note on 1.1 V to consider increasing to 1.15 V added 150 uF caps on Vbus added 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
2020-07-29 directly ground USB A connectors
2020-07-29 use dual diodes in keyboard matrix
2020-07-31 change to USB mid mount, misc add AC coupling caps to A connectors change programming header to tag connect
2020-08-04 100% routed needs: review intra pair delay matching ground cutouts fab notes
2020-08-10 PCB diff pair skew, cutouts, etc arrange silkscreen ground plane cutouts under large high speed pads intra pair skew matching general cleanup
2020-08-11 correct USB A part number, add inductor part number
2020-08-11 fix min solder mask width this was causing no mask to be present between a few QFN ground pads and leads
2020-09-02 remove key matrix ESD note issue #6
2020-09-02 correct 1.1 V supply set point resistors closes #2
2020-09-02 use PE2 for LED instead of key matrix closes #7 @jackpot51, note some column lines were swapped for layout purposes
2020-09-02 fix Kailh_socket footprint Put the SMD pads on the top layer so it appears in the correct pick and place file Flipped the entire footprint, then all instances of it on the PCB. closes #1
2020-09-02 remove unused footprints
2020-09-02 reduce paste mask opening size by 25 μm on USB7206 Issue #5
2020-09-02 flip 3D models in key footprint too Issue #1
2020-09-02 Use smaller LEDs for key clearance Issue #8 Increased 3.6 V supply to 3.74 V to support new LEDs LEDs moved to 5.05 mm above center peg of key
2020-09-02 add LED decoupling Issue #8
2020-09-03 adjust exposed pad solder paste to NXP suggested
2020-09-09 Change SS mux to CBTL02043 for larger easier to solder footprint control IO moved from the TCPCs to the USB hub closes #4
2020-09-09 adjust trace widths, stackup for as-built controlled impedance
2020-09-09 Add additional solder paste are to pin in paste pads to increase solder volume and/or allow for a solder preform to be placed
2020-09-09 add 3D models for remaining parts
2020-09-09 better distibution of LED decoupling
2020-09-10 add ground cutouts on CL SS Mux
2020-09-10 ESD protection datasheet
2020-09-10 ignore generated step file
2020-09-10 schematic cleanup no electrical changes fix overlapping text add notes add manufacturer part number for AVR crystal
2020-09-17 ground cutouts, ground plane continuity Add ground plane cutouts on D1 Add small ground plane cutouts on USB7206 move 2 vias near U15 slightly to improve ground plane continuity
2020-09-18 BOM update Add manufacturer info Add key socket PN Correct USB-A to surface mount (was through hole)
2020-09-18 move USB A down 2.1 mm
2020-09-18 plated mounting holes adjust position of one mounting hole slightly add hole near middle.
2020-09-18 BOM with USB hub
2020-09-27 Adjustments for production Change laminate from ITEQ IT180A to Shengyi S1000-2 - Associated controlled impedance changes Remove circles on Cmts.User in mounting holes that were confusing manufacturer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
2020-10-10 clean up fab layers for assembler
2020-10-21 Add qmk script
2020-10-28 change VBUS caps to as-built part is taller
2020-11-05 Add disk benchmarking script
2020-11-11 increase size of USB C pads for hand soldering only pads on opposite side of connector
2020-11-11 fix DRC error
2020-11-11 Add System76 logo and board revision
2020-11-11 Update board revision in comments
2021-01-23 LVFS firmware generation
2021-01-23 Use QMK firmware version to populate LVFS information
2021-01-23 Fixes for lvfs metadata
2021-01-24 Fix source URL in LVFS metadata
2021-01-24 Add lvfs version format
2021-01-24 Rename launch_beta_1 to launch_1
2021-01-25 Add production firmware script
2021-02-02 Remove bootloader UUID from lvfs metadata
2021-02-02 Do not include hex or bin file in lvfs archive
2021-02-09 Add README
2021-02-09 Add .step to lfs
2021-02-09 Add licenses, create chassis directory
2021-02-09 Add chassis CAD and drawings
2021-02-10 Write readme and reorganize
2021-02-11 Move LICENSE.md file from pcb directory to root
2021-02-15 Add some packaging and regulatory info
2021-02-15 Add packaging reference CAD
2021-02-15 Packaging dielines
2021-02-17 Reconfigure pcb to use A3 page size and measure the pcb
2021-02-17 Update package label with OSHWA number
2021-02-17 Add OSHWA UID
2021-02-17 Track .ai files in GIT LFS
2021-04-01 Update firmware
2021-05-20 add copper areas to switch pads this should help prevent them from tearing off if a key is misaligned or has bent pins when inserted
2021-05-20 add components to support USB7216 The USB7216 uses an alternate location, pin 80 for VBUS monitoring. This adds a voltage divider, R18 and R28 which should only be installed if a USB7216 is used. Pad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
2021-05-20 add minimum thickness for outer copper It's in IPC-A-600, but adding to be clear there is a minimum copper requirement
2021-05-20 revert accidental removal of System76 logo
2021-05-20 add logo to schematic, link with PCB
2021-05-20 update BOM with added resistors for USB7206
2021-05-20 update BOM for United Chemi-Con VBUS caps
2021-05-21 Ensure correct VBUS capacitor part number
2021-05-21 Add AP3441LSHE-7B docs, symbol, and footprint
2021-05-21 Correct VBUS capacitors model
2021-05-21 Switch to AP3441LSHE-7B in PCB
2021-05-21 Switch to AP3441LSHE-7B in BOM
2021-05-21 Switch to AP3441LSHE-7B in schematic
2021-05-21 Add 22pF capacitors to AP3441-L as recommended
2021-05-26 Add AP61302 regulator symbol and datasheet
2021-05-26 Add script for calculating AP61302 parameters
2021-05-26 Use AP61302 for regulating 1V1 and 3V6 power planes
2021-05-27 minor layout adjustments, feedforward cap value Change feedforward cap to 330 pF so the transfer function of the feedback network will be similar to that of the datasheet example. Our feedback resist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
    Correct typo in notes on power schematic page.
    Change buck feedforward cap footprint from Kicad lib to launch lib for consistency.
    Arrange schematic components so "330 pF" does not overlap adjacent components.
    Move "U4" silkscreen to not overlap inductor pad.
    Add a 2nd via to each buck converter ground, move feedback components to allow.
    Reroute some signal traces to reduce number of vias, have more solid grou
2021-06-25 Track .f3d using GIT LFS
2021-06-25 Add native chassis files
2021-06-25 Add cache library
    The cache library needs to be kept around for several reasons:
    - make the project independent of the system libraries
    - ensure readability with future KiCad versions
2021-07-30 Add CNC setup instructions
2021-09-13 Fix library references for symbols renamed in upstream also remove cache from gitignore, include in repo in case user's libaries don't align.
2021-09-14 use AP3441LSHE-7B DC-DC switching to available part from long lead time part adds 2 22 uF 0805 capacitors as well
2021-09-14 add PDF schematic #39
2021-09-14 remove PDF schematic
2021-12-03 add initial lite design based on standard launch uses AT90USB646 (more pins, availability no USB hub relaxes PCB requirements to 5/5 mil track, space, 0.5/0.25 mm vias
2021-12-08 launch lite finalization set version to 1.0 copper to NPTH clearance increased to 0.5 mm reroute a few traces move entire PCB by 50, 50 mm to get off of sheet frame
2021-12-08 refilled polygons this corresponds to the gerbers, was not checked in with last commit
2022-03-09 Update firmware and add lite LED script
2022-03-09 Add LVFS script for lite, update firmware
2022-03-18 Add launch_lite_1_0 chassis
2022-04-04 Fix launch chassis broken image in README
2022-05-02 move to Kicad 6, share libs with lite
2022-05-02 add MT3410LB to symbol library
2022-05-10 tenkey work in progress needs via stitching, decoupling, cleanup, etc
2022-05-10 document part replacements
2022-05-10 work in progress toward 2.0
2022-05-19 version pins, finalize routing FFC connector changed to 20 pin USB hub reset pull down via stitching route remaining nets and cleanup
2022-05-19 rename launch-tenkey to launch-heavy
2022-05-24 set versions
2022-05-24 remove files associated with old versions
2022-05-24 fix typo in part substitutions
2022-05-24 create lite-ISO
2022-05-24 set version, change ISO to lower case in silkscreen
2022-05-24 change USB7216 to USB7006
2022-06-06 Update launch_lite_1_0 chassis CAD and Drawings
2022-06-17 Fix LVFS scripts
2022-06-21 Add Launch Lite packaging and regulatory
2022-06-23 Make lvfs/production script support passing model name
2022-08-03 radius switch pads for more clearance
2022-08-03 launch heavy 1.1 move mounting holes to allow room for stabilizers no schematic changes round switch pads for improved clearance relocate D14 for mounting hole clearance
2022-08-13 launch-iso based on launch 2.0 remove unused mounting holes add diode footprint to local lib as the Kicad one changed
2022-08-16 clean up routing, schematic title block
2022-09-30 Add launch_2_0 packaging label
2022-10-19 Add Launch Heavy chassis
2022-10-21 Add launch heavy led matrix script
2022-10-24 Add Launch Heavy packaging label tempate
2022-11-16 Update firmware submodule for launch_2 and launch_heavy_1
2022-11-16 Add Heavy to lvfs.sh script
2022-12-07 rotate +, enter on heavy, move hole
2023-01-31 save in Kicad 7 format
2023-01-31 RP2040, USB7216 Change USB hub part number to USB7216 Change microcontroller to RP2040 remove vbus switch for microcontroller as RP2040 does not require vbus sensing
2023-01-31 use .step models instead of .wrl Kicad 7 STEP export can't handle the .wrl files that were the default in 6 ran sed -i 's/wrl/step/g' launch.kicad_pcb
2023-01-31 fix swapped SDA, SCL at U1 fix parts overhanging schematic edge
2023-02-03 resolve schematic ERC
2023-02-03 change AVR to UC on some net names since we don't have an Atmel AVR controller now
2023-02-03 add 2nd SWD connector, BOM edits, export
2023-05-04 launch 3.1 LED ESD mitigation - ground plane on top, move some traces to inner add cutouts to make removing from chassis easier AP22802 is no longer an allowed substitution
2023-05-04 hub reset handled by DC-DC power good switch to TLV62585P DC-DC for power good remove reset button - can just plug cable add buttons to ground SDA, SCL as hub bypass to allow programming
2023-05-08 single button for DFU boot also some ground stitching
2023-05-11 BOM update USB7206CT/KDX, TLV62585PDRLR
2023-05-18 Update firmware version
2023-08-25 lvfs: require fwupd 1.9.5 or greater
2023-08-30 VBUS protection circuitry add capacitors at every USB power switch add reverse protection schottky diode to clamp observed negative voltages seen on VBUS during plug and unplug add RC snubber to VBUS
2023-08-30 Add script for UF2 LVFS firmware
2023-08-31 change boot button to lower profile
2025-07-02 Updated FreeCAD address.
